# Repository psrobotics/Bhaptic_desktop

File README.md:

# Bhaptic_desktop

Bhaptic_desktop is a open-sorce, low-cost 3DOF desktop haptic device like [PHAToM haptic device](https://alliance.seas.upenn.edu/~medesign/wiki/uploads/Courses/Massie94-DSC-Phantom.pdf). It allows user to interact with the virtual while feeling the feedback force. It's an old project back in 2019.

## Videos

## File Structure

* /hardware - CAD, STL exports, CAM file

* /electronic - Motor driver, Encoder reader

* /software - Arduino Firmware, PCL interface

## Pics

### [Motor](https://product.minebeamitsumi.com/en/product/category/rotary/brushmotor/dc/parts/M36N5E.html)

### Controller

### Docu

## License
MIT License

## Contact
* Shuang Peng, {shuangpe}@usc.edu

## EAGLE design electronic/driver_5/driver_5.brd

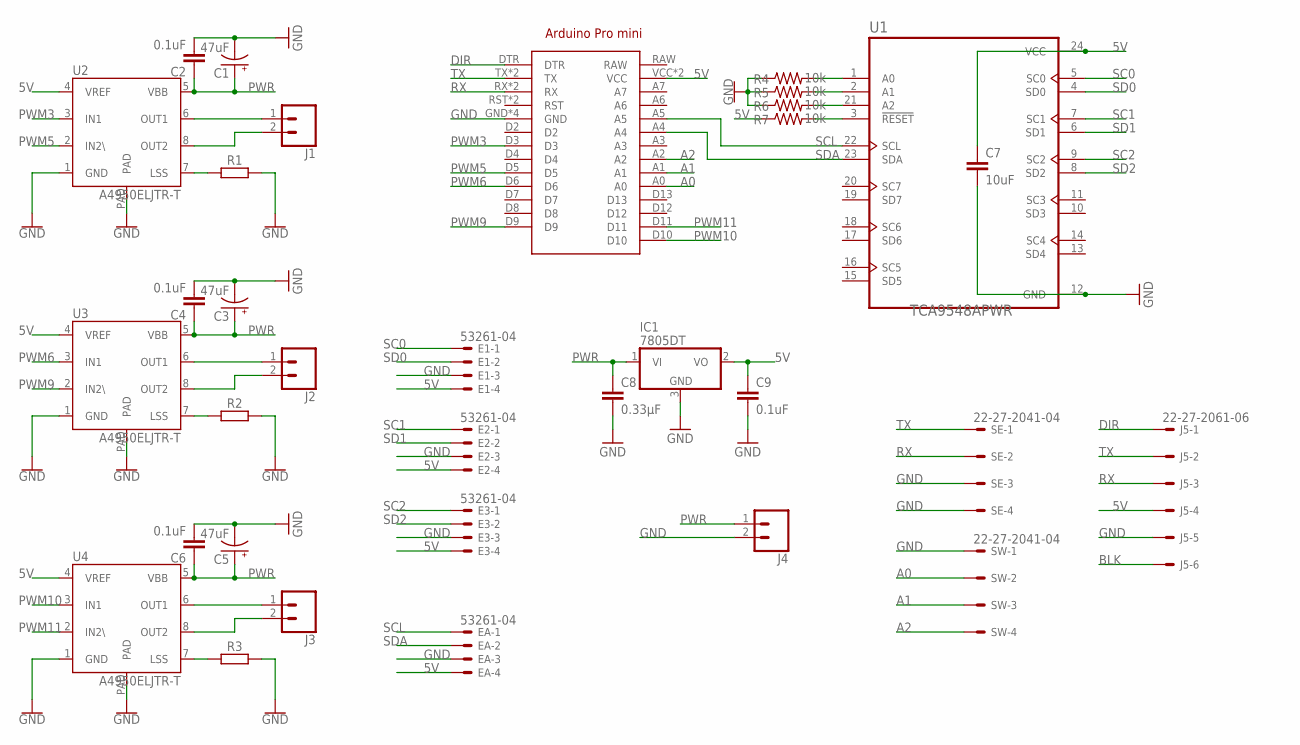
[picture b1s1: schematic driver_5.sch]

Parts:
ARDUINO1: ARDUINO_PRO_MINI
C1, C3, C5: 47uF; EIA3528
C2, C4, C6: 0.1uF; 0402
C7: 10uF; 0603
C8: 0.33µF; 0805
C9: 0.1uF; 0603
E1, E2, E3: 53261-04
EA: 53261-04
IC1: 7805DT; TO252
J1, J2, J3, J4: CONN_025MM; SCREWTERMINAL-5MM-2
J5: 22-27-2061-06; 6410-06
R1, R2, R3: 0.22; R2512
R4, R5, R6, R7: 10k; 0603
SE: 22-27-2041-04; 6410-04
SW: 22-27-2041-04; 6410-04
U1: TCA9548APWR; SOP65P640X120-24N
U2, U3, U4: A4950ELJTR-T; SOIC8TP

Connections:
5V: ARDUINO1.VCC, ARDUINO1.VCC@1 (VCC), C7.1, C9.1, E1.4, E2.4, E3.4, EA.4, IC1.2 (VO), J5.4, R7.1, U1.24 (VCC), U2.4 (VREF), U3.4 (VREF), U4.4 (VREF)
A0: ARDUINO1.A0, SW.2
A1: ARDUINO1.A1, SW.3
A2: ARDUINO1.A2, SW.4
BLK: J5.6
DIR: ARDUINO1.DTR, J5.1
GND: ARDUINO1.GND, ARDUINO1.GND@1 (GND), ARDUINO1.GND@2 (GND), ARDUINO1.GND@3 (GND), C1.C (-), C2.2, C3.C (-), C4.2, C5.C (-), C6.2, C7.2, C8.2, C9.2, E1.3, E2.3, E3.3, EA.3, IC1.3 (GND), J4.2, J5.5, R1.2, R2.2, R3.2, R4.1, R5.1, R6.1, SE.3, SE.4, SW.1, U1.12 (GND), U2.1 (GND), U2.PAD, U3.1 (GND), U3.PAD, U4.1 (GND), U4.PAD
unnamed: R1.1, U2.7 (LSS)
unnamed: R4.2, U1.1 (A0)
unnamed: J1.1, U2.6 (OUT1)
unnamed: J1.2, U2.8 (OUT2)
unnamed: R2.1, U3.7 (LSS)
unnamed: J2.1, U3.6 (OUT1)
unnamed: J2.2, U3.8 (OUT2)
unnamed: R3.1, U4.7 (LSS)
unnamed: J3.1, U4.6 (OUT1)
unnamed: J3.2, U4.8 (OUT2)
unnamed: R5.2, U1.2 (A1)
unnamed: R6.2, U1.21 (A2)
unnamed: R7.2, U1.3 (!RESET)
PWM3: ARDUINO1.D3, U2.3 (IN1)
PWM5: ARDUINO1.D5, U2.2 (IN2\)
PWM6: ARDUINO1.D6, U3.3 (IN1)
PWM9: ARDUINO1.D9, U3.2 (IN2\)
PWM10: ARDUINO1.D10, U4.3 (IN1)
PWM11: ARDUINO1.D11, U4.2 (IN2\)
PWR: C1.A (+), C2.1, C3.A (+), C4.1, C5.A (+), C6.1, C8.1, IC1.1 (VI), J4.1, U2.5 (VBB), U3.5 (VBB), U4.5 (VBB)
RX: ARDUINO1.RX, ARDUINO1.RX@1 (RX), J5.3, SE.2
SC0: E1.1, U1.5 (SC0)
SC1: E2.1, U1.7 (SC1)
SC2: E3.1, U1.9 (SC2)
SCL: ARDUINO1.A5, EA.1, U1.22 (SCL)
SD0: E1.2, U1.4 (SD0)
SD1: E2.2, U1.6 (SD1)
SD2: E3.2, U1.8 (SD2)
SDA: ARDUINO1.A4, EA.2, U1.23 (SDA)
TX: ARDUINO1.TX, ARDUINO1.TX@1 (TX), J5.2, SE.1

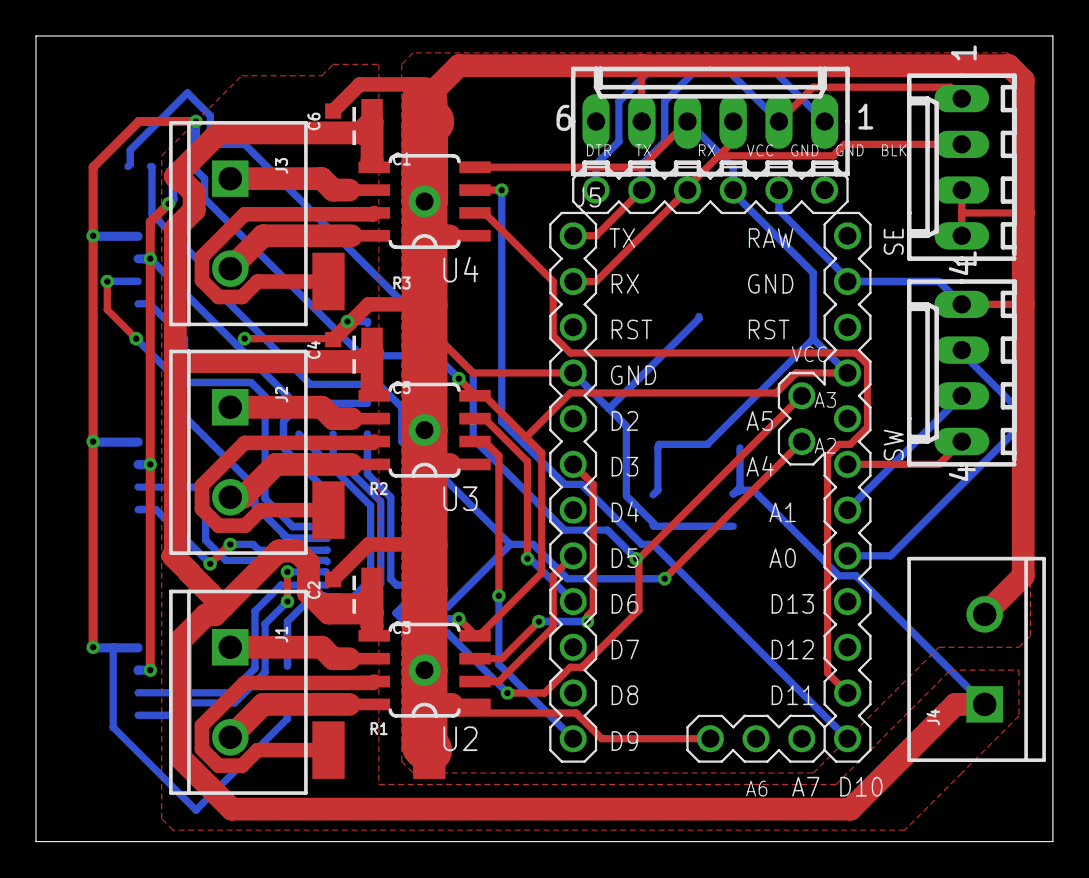
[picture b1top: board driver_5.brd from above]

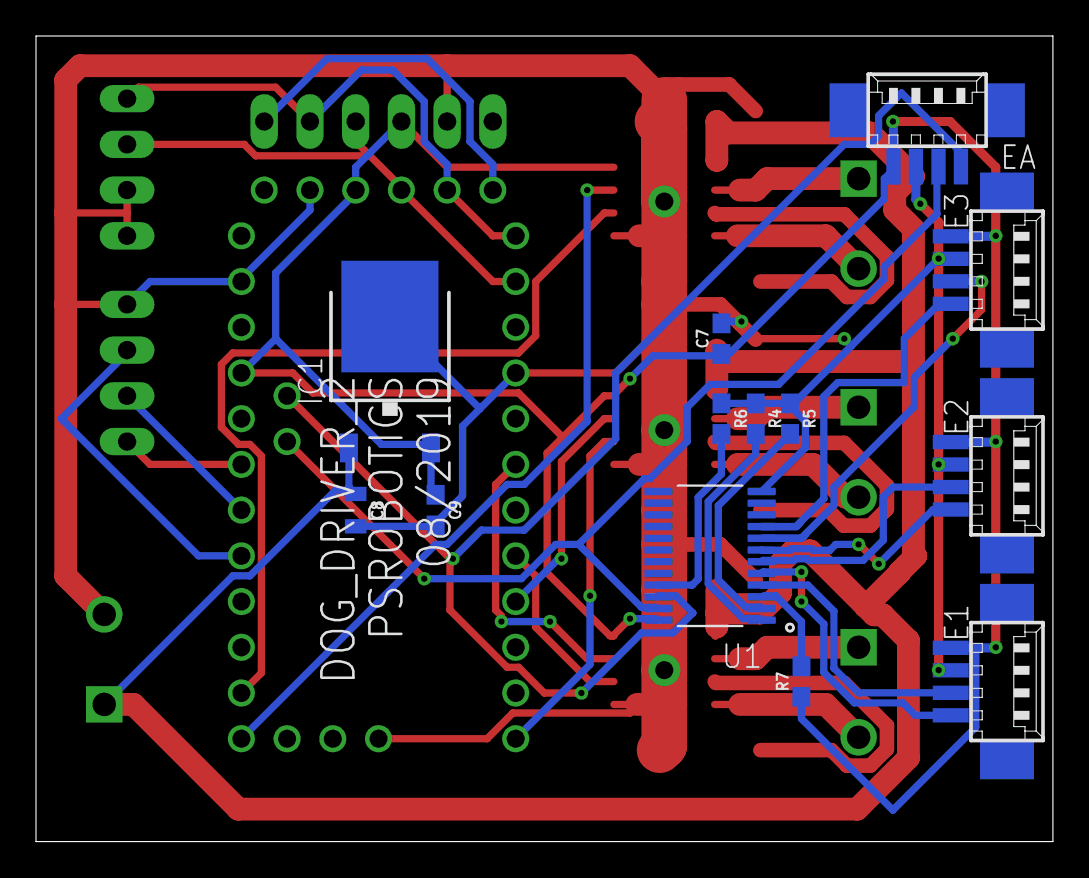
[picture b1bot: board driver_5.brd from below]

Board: 2 copper layers, 56.5 x 44.8 mm, 33 parts (13 on the bottom side), 36 nets.

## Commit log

2024-03-05 init: 0305

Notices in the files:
parts and their libraries:
SparkFun-Capacitors: Licensing: Creative Commons ShareAlike 4.0 International - https://creativecommons.org/licenses/by-sa/4.0
